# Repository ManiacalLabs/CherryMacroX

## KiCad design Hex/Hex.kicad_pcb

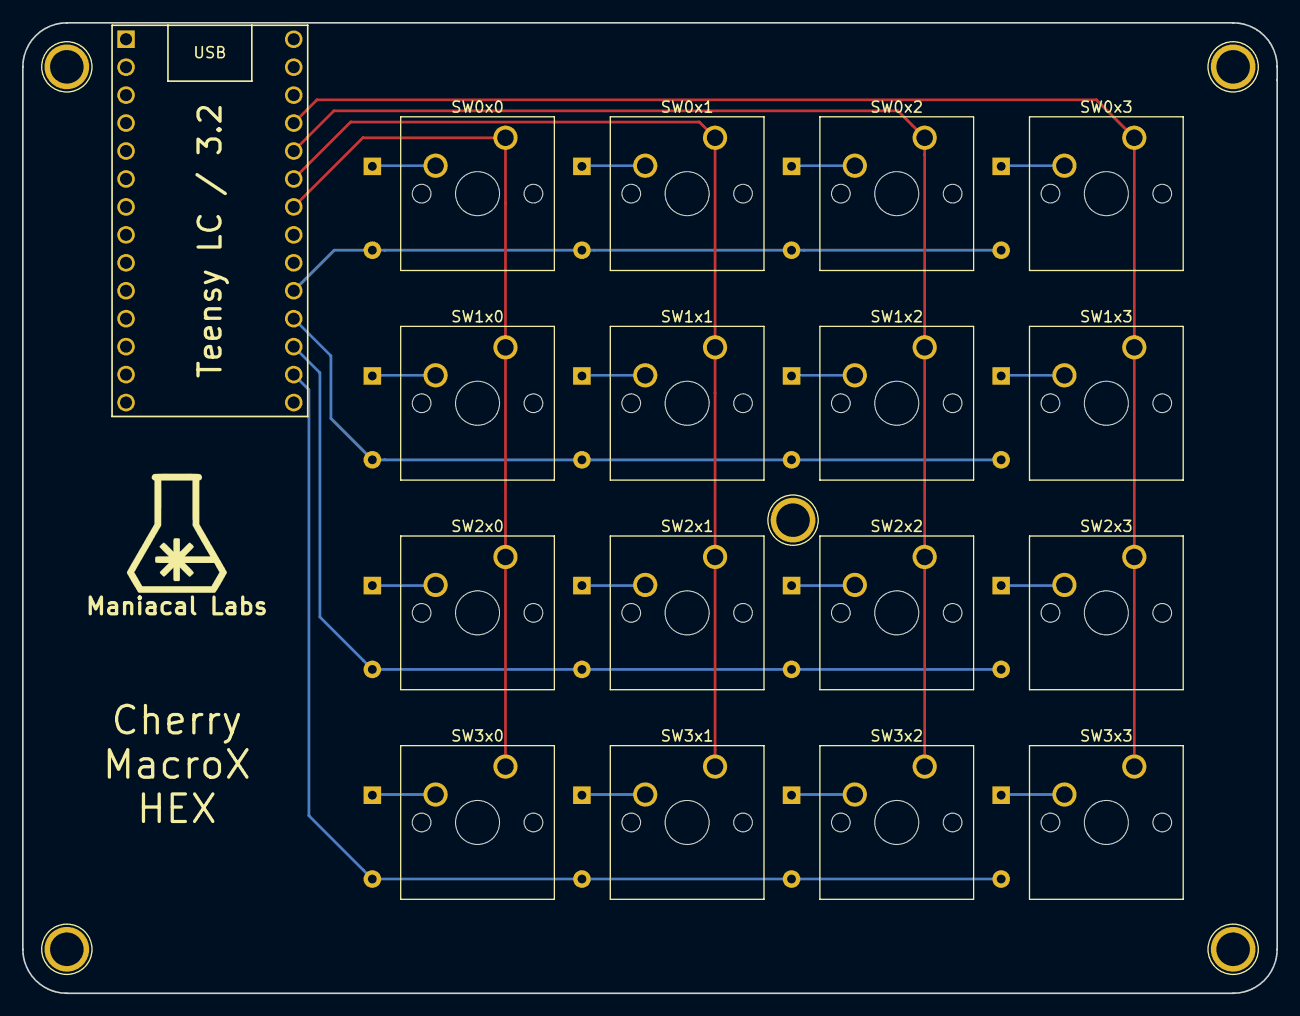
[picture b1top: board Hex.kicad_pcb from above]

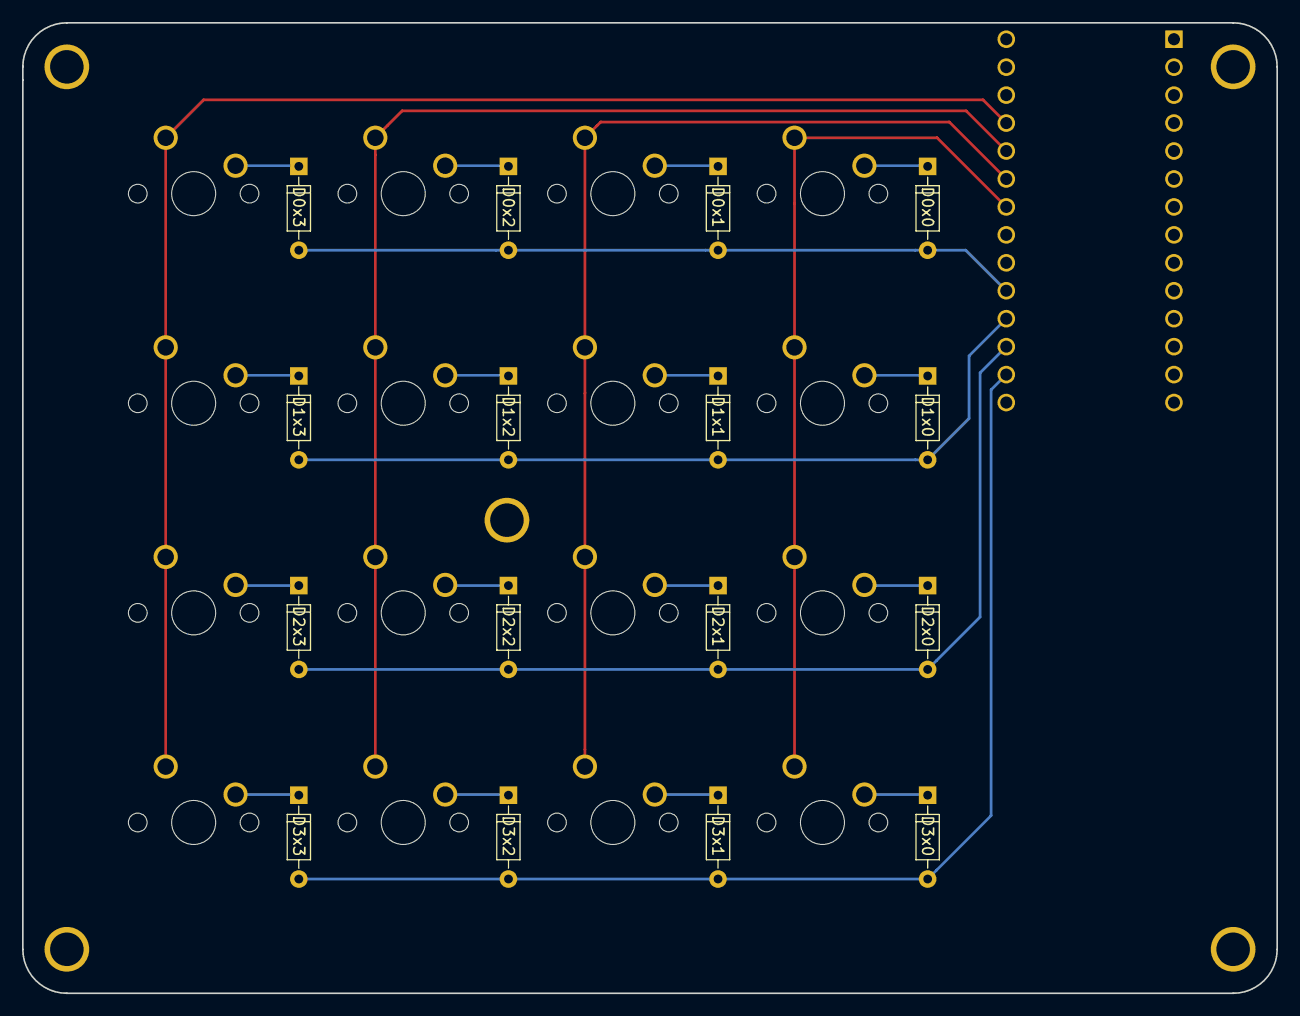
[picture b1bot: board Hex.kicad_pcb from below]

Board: 2 copper layers, 114.0 x 88.2 mm, 34 parts (16 on the bottom side), 24 nets.

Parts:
D0x0, D0x1, D0x2, D0x3, D1x0, D1x1, D1x2, D1x3, D2x0, D2x1, D2x2, D2x3, D3x0, D3x1, D3x2, D3x3: 1N4148; D_DO-35_SOD27_P7.62mm_Horizontal
L103: Maniacal Labs; logo_MLlabs
SW0x0, SW0x1, SW0x2, SW0x3, SW1x0, SW1x1, SW1x2, SW1x3, SW2x0, SW2x1, SW2x2, SW2x3, SW3x0, SW3x1, SW3x2, SW3x3: SW_Push; SW_Cherry_MX1A_1.00u_PCB
U1: Teensy-LC; Teensy30_31_32_LC_Simple

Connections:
COL_0: SW0x0.1, SW1x0.1, SW2x0.1, SW3x0.1, U1.27
COL_1: SW0x1.1, SW1x1.1, SW2x1.1, SW3x1.1, U1.28
COL_2: SW0x2.1, SW1x2.1, SW2x2.1, SW3x2.1, U1.29
COL_3: SW0x3.1, SW1x3.1, SW2x3.1, SW3x3.1, U1.30
unnamed: D0x0.1, SW0x0.2
unnamed: D0x1.1, SW0x1.2
unnamed: D0x2.1, SW0x2.2
unnamed: D0x3.1, SW0x3.2
unnamed: D1x0.1, SW1x0.2
unnamed: D1x1.1, SW1x1.2
unnamed: D1x2.1, SW1x2.2
unnamed: D1x3.1, SW1x3.2
unnamed: D2x0.1, SW2x0.2
unnamed: D2x1.1, SW2x1.2
unnamed: D2x2.1, SW2x2.2
unnamed: D2x3.1, SW2x3.2
unnamed: D3x0.1, SW3x0.2
unnamed: D3x1.1, SW3x1.2
unnamed: D3x2.1, SW3x2.2
unnamed: D3x3.1, SW3x3.2
ROW_0: D0x0.2, D0x1.2, D0x2.2, D0x3.2, U1.24
ROW_1: D1x0.2, D1x1.2, D1x2.2, D1x3.2, U1.23
ROW_2: D2x0.2, D2x1.2, D2x2.2, D2x3.2, U1.22
ROW_3: D3x0.2, D3x1.2, D3x2.2, D3x3.2, U1.21

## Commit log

2018-09-16 Removing old labels
2018-09-16 move logos
